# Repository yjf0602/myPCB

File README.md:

# myPCB
Some PCB projects.

1. [usb_uart_cp2102](usb_uart_cp2102/) is a small usb-uart convert board with chip CP2102. It can be hung on the key chain.

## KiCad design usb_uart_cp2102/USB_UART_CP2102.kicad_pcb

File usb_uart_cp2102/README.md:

## usb_uart_cp2102 

Kicad 5.1 project.

### lyaout

### 3D Render

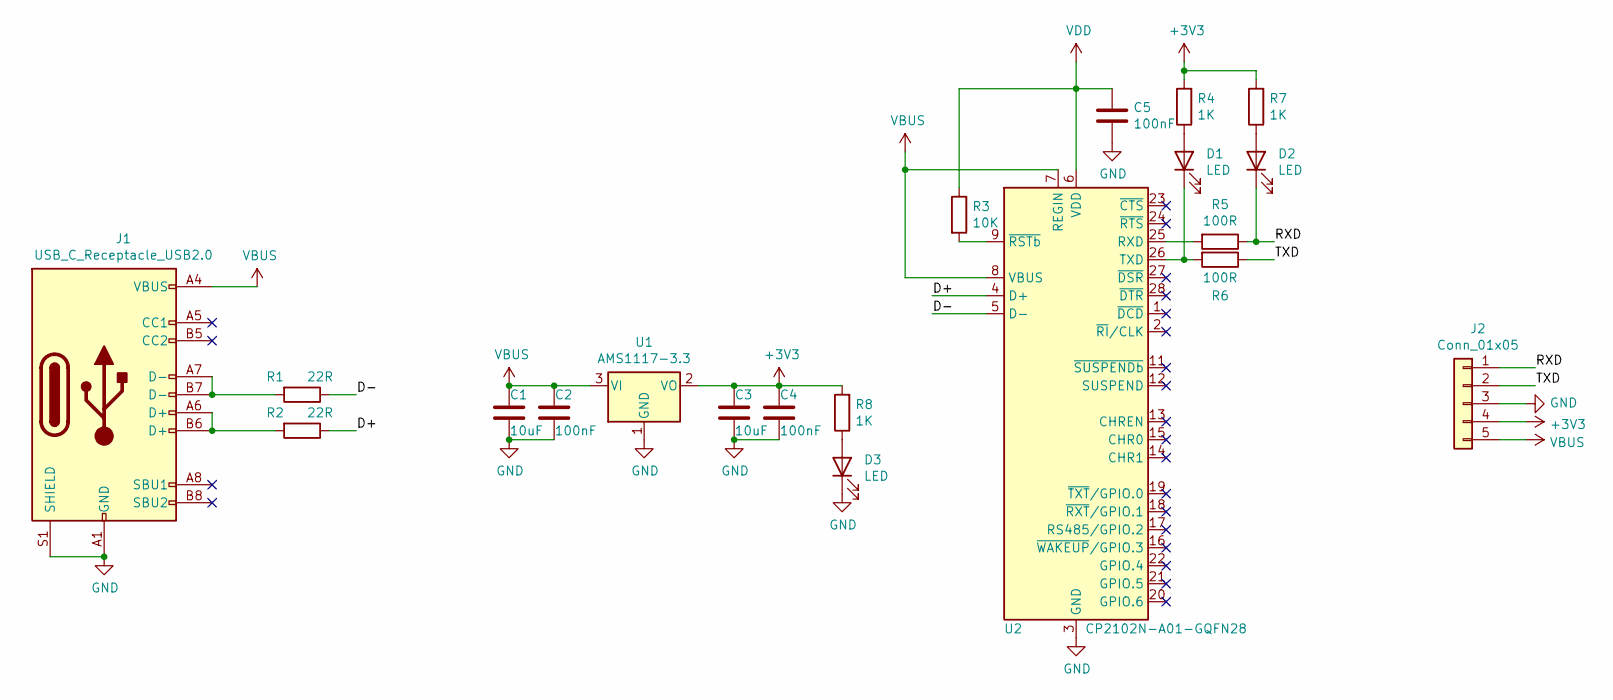
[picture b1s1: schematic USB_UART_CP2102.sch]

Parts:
C1, C3: 10uF; C_0603_1608Metric
C2, C4, C5: 100nF; C_0603_1608Metric
D1, D2, D3: LED; LED_0603_1608Metric
J1: USB_C_Receptacle_USB2.0; USB_C_Receptacle_Palconn_UTC16-G
J2: Conn_01x05; PinHeader_1x05_P2.54mm_Horizontal
R1, R2: 22R; R_0603_1608Metric
R3: 10K; R_0603_1608Metric
R4, R7, R8: 1K; R_0603_1608Metric
R5, R6: 100R; R_0603_1608Metric
U1: AMS1117-3.3; SOT-223-3_TabPin2
U2: CP2102N-A01-GQFN28; QFN-28-1EP_5x5mm_P0.5mm_EP3.35x3.35mm

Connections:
+3V3: C3.1, C4.1, J2.4, R4.2, R7.2, R8.2, U1.2 (VO)
/D+: R2.1, U2.4 (D+)
/D-: R1.1, U2.5 (D-)
/RXD: D2.1 (K), J2.1, R5.1
/TXD: J2.2, R6.1
GND: C1.2, C2.2, C3.2, C4.2, C5.2, D3.1 (K), J1.A1 (GND), J1.A12 (GND), J1.B1 (GND), J1.B12 (GND), J1.S1 (SHIELD), J2.3, U1.1 (GND), U2.3 (GND), U2.29 (GND)
unnamed: D1.1 (K), R6.2, U2.26 (TXD)
unnamed: D1.2 (A), R4.1
unnamed: D2.2 (A), R7.1
unnamed: D3.2 (A), R8.1
unnamed: J1.A6 (D+), J1.B6 (D+), R2.2
unnamed: J1.A7 (D-), J1.B7 (D-), R1.2
unnamed: R3.2, U2.9 (~RSTb)
unnamed: R5.2, U2.25 (RXD)
VBUS: C1.1, C2.1, J1.A4 (VBUS), J1.A9 (VBUS), J1.B4 (VBUS), J1.B9 (VBUS), J2.5, U1.3 (VI), U2.7 (REGIN), U2.8 (VBUS)
VDD: C5.1, R3.1, U2.6 (VDD)

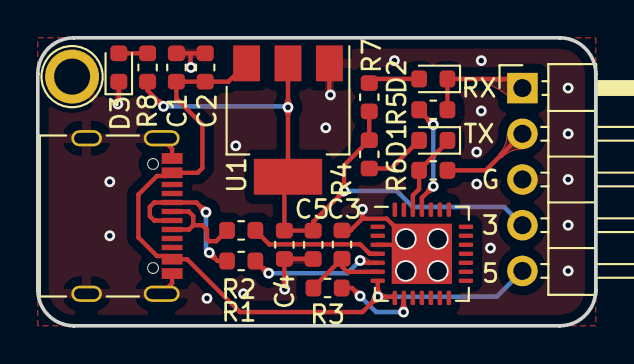
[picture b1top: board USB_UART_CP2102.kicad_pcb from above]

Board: 2 copper layers, 31.0 x 16.0 mm, 20 parts (0 on the bottom side), 16 nets.

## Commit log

2021-01-01 add usb_uart_cp2102 project.
2021-01-01 modify usb_uart_cp2102/README.md
